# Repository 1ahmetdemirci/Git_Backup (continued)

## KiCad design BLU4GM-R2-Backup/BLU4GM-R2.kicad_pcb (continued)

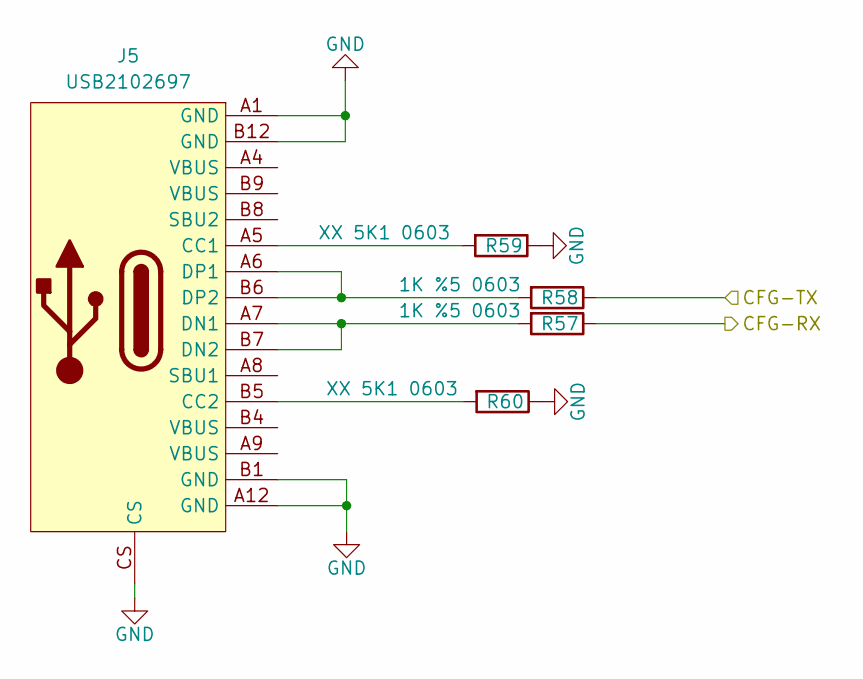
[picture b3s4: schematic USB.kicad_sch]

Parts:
J5: USB2102697
R57, R58: 1K %5 0603; R_0603_1608Metric
R59, R60: XX 5K1 0603; R_0603_1608Metric

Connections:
/MCU/CFG-RX: R57.1; also elsewhere on the board
/MCU/CFG-TX: R58.1; also elsewhere on the board
GND: J5.A1 (GND), J5.A12 (GND), J5.B1 (GND), J5.B12 (GND), J5.CS, R59.1, R60.1; also elsewhere on the board
unnamed: J5.A5 (CC1), R59.2
unnamed: J5.B5 (CC2), R60.2
unnamed: J5.A7 (DN1), J5.B7 (DN2), R57.2
unnamed: J5.A6 (DP1), J5.B6 (DP2), R58.2

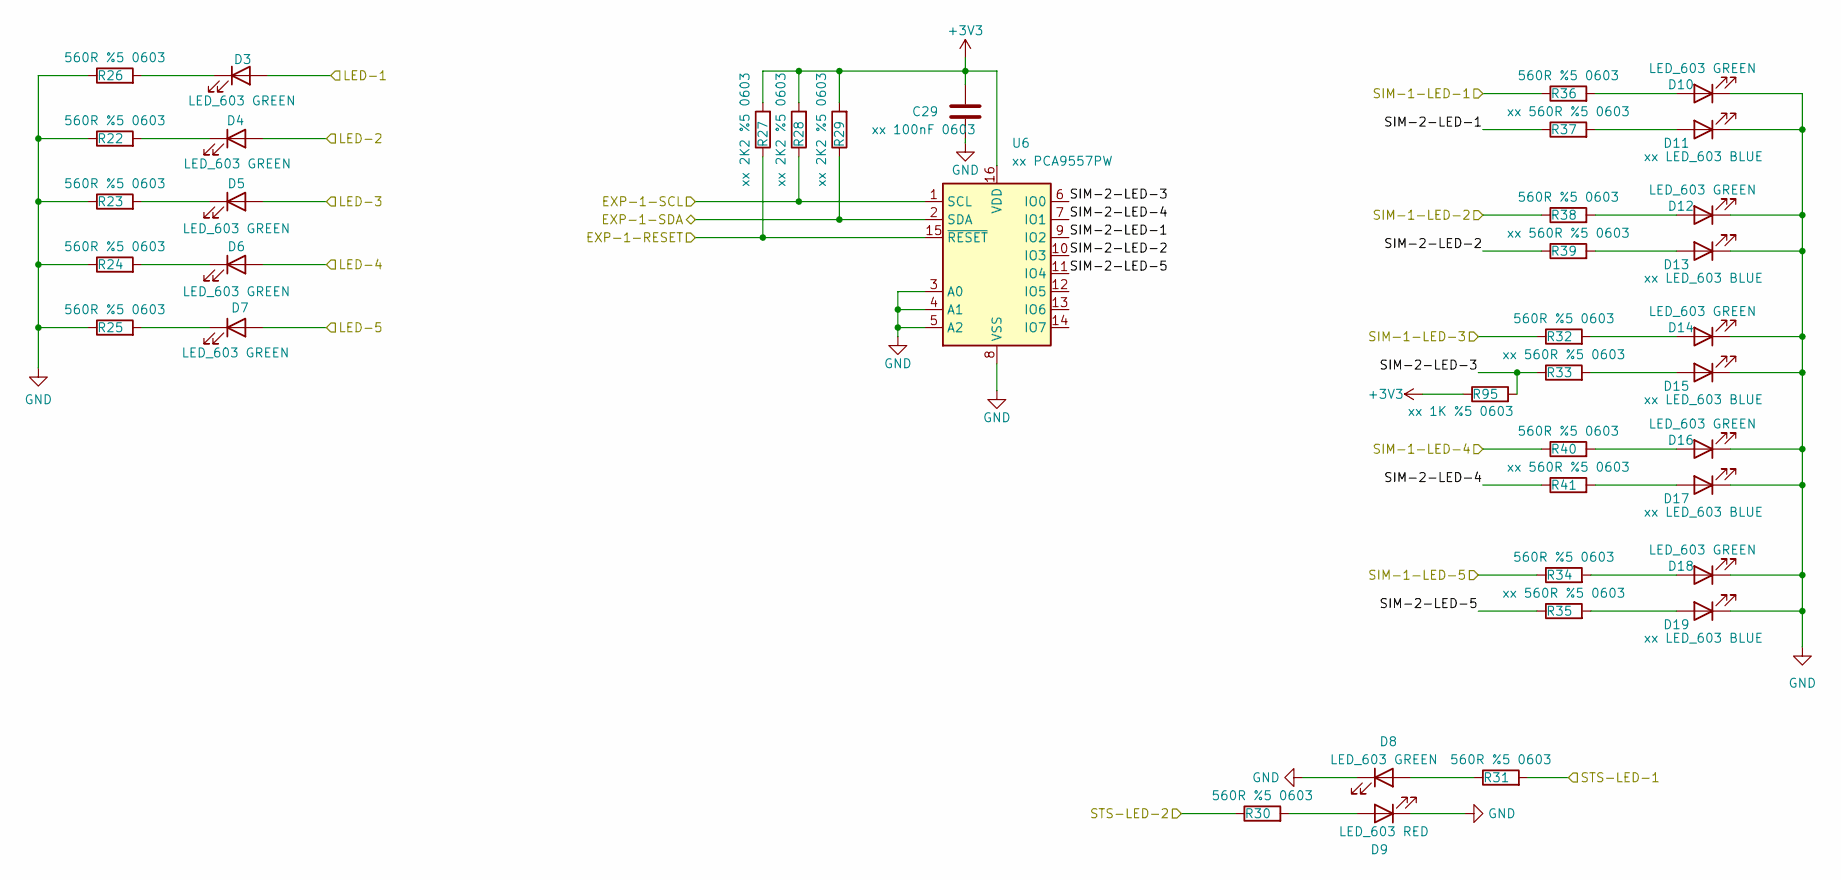
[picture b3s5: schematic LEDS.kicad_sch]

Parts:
C29: xx 100nF 0603; C_0603_1608Metric
D3, D4, D5, D6, D7, D8, D10, D12, D14, D16, D18: LED_603 GREEN; LED_0603_1608Metric
D9: LED_603 RED; LED_0603_1608Metric
D11, D13, D15, D17, D19: xx LED_603 BLUE; LED_0603_1608Metric
R22, R23, R24, R25, R26, R30, R31, R32, R34, R36, R38, R40: 560R %5 0603; R_0603_1608Metric
R27, R28, R29: xx 2K2 %5 0603; R_0603_1608Metric
R33, R35, R37, R39, R41: xx 560R %5 0603; R_0603_1608Metric
R95: xx 1K %5 0603; R_0603_1608Metric
U6: xx PCA9557PW; TSSOP-16_4.4x5mm_P0.65mm

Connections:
+3V3: C29.1, R27.2, R28.2, R29.2, R95.1, U6.16 (VDD); also elsewhere on the board
/LEDS/EXP-1-RESET: R27.1, U6.15 (~RESET); also elsewhere on the board
/LEDS/EXP-1-SCL: R28.1, U6.1 (SCL); also elsewhere on the board
/LEDS/EXP-1-SDA: R29.1, U6.2 (SDA); also elsewhere on the board
/LEDS/LED-1: D3.2 (A); also elsewhere on the board
/LEDS/LED-2: D4.2 (A); also elsewhere on the board
/LEDS/LED-3: D5.2 (A); also elsewhere on the board
/LEDS/LED-4: D6.2 (A); also elsewhere on the board
/LEDS/LED-5: D7.2 (A); also elsewhere on the board
/LEDS/SIM-1-LED-1: R36.1; also elsewhere on the board
/LEDS/SIM-1-LED-2: R38.1; also elsewhere on the board
/LEDS/SIM-1-LED-3: R32.1; also elsewhere on the board
/LEDS/SIM-1-LED-4: R40.1; also elsewhere on the board
/LEDS/SIM-1-LED-5: R34.1; also elsewhere on the board
/LEDS/SIM-2-LED-1: R37.1, U6.9 (IO2)
/LEDS/SIM-2-LED-2: R39.1, U6.10 (IO3)
/LEDS/SIM-2-LED-3: R33.1, R95.2, U6.6 (IO0)
/LEDS/SIM-2-LED-4: R41.1, U6.7 (IO1)
/LEDS/SIM-2-LED-5: R35.1, U6.11 (IO4)
/LEDS/STS-LED-1: R31.2; also elsewhere on the board
/LEDS/STS-LED-2: R30.1; also elsewhere on the board
GND: C29.2, D8.1 (K), D9.1 (K), D10.1 (K), D11.1 (K), D12.1 (K), D13.1 (K), D14.1 (K), D15.1 (K), D16.1 (K), D17.1 (K), D18.1 (K), D19.1 (K), R22.1, R23.1, R24.1, R25.1, R26.1, U6.3 (A0), U6.4 (A1), U6.5 (A2), U6.8 (VSS); also elsewhere on the board
unnamed: D3.1 (K), R26.2
unnamed: D4.1 (K), R22.2
unnamed: D5.1 (K), R23.2
unnamed: D6.1 (K), R24.2
unnamed: D7.1 (K), R25.2
unnamed: D8.2 (A), R31.1
unnamed: D9.2 (A), R30.2
unnamed: D10.2 (A), R36.2
unnamed: D11.2 (A), R37.2
unnamed: D12.2 (A), R38.2
unnamed: D13.2 (A), R39.2
unnamed: D14.2 (A), R32.2
unnamed: D15.2 (A), R33.2
unnamed: D16.2 (A), R40.2
unnamed: D17.2 (A), R41.2
unnamed: D18.2 (A), R34.2
unnamed: D19.2 (A), R35.2

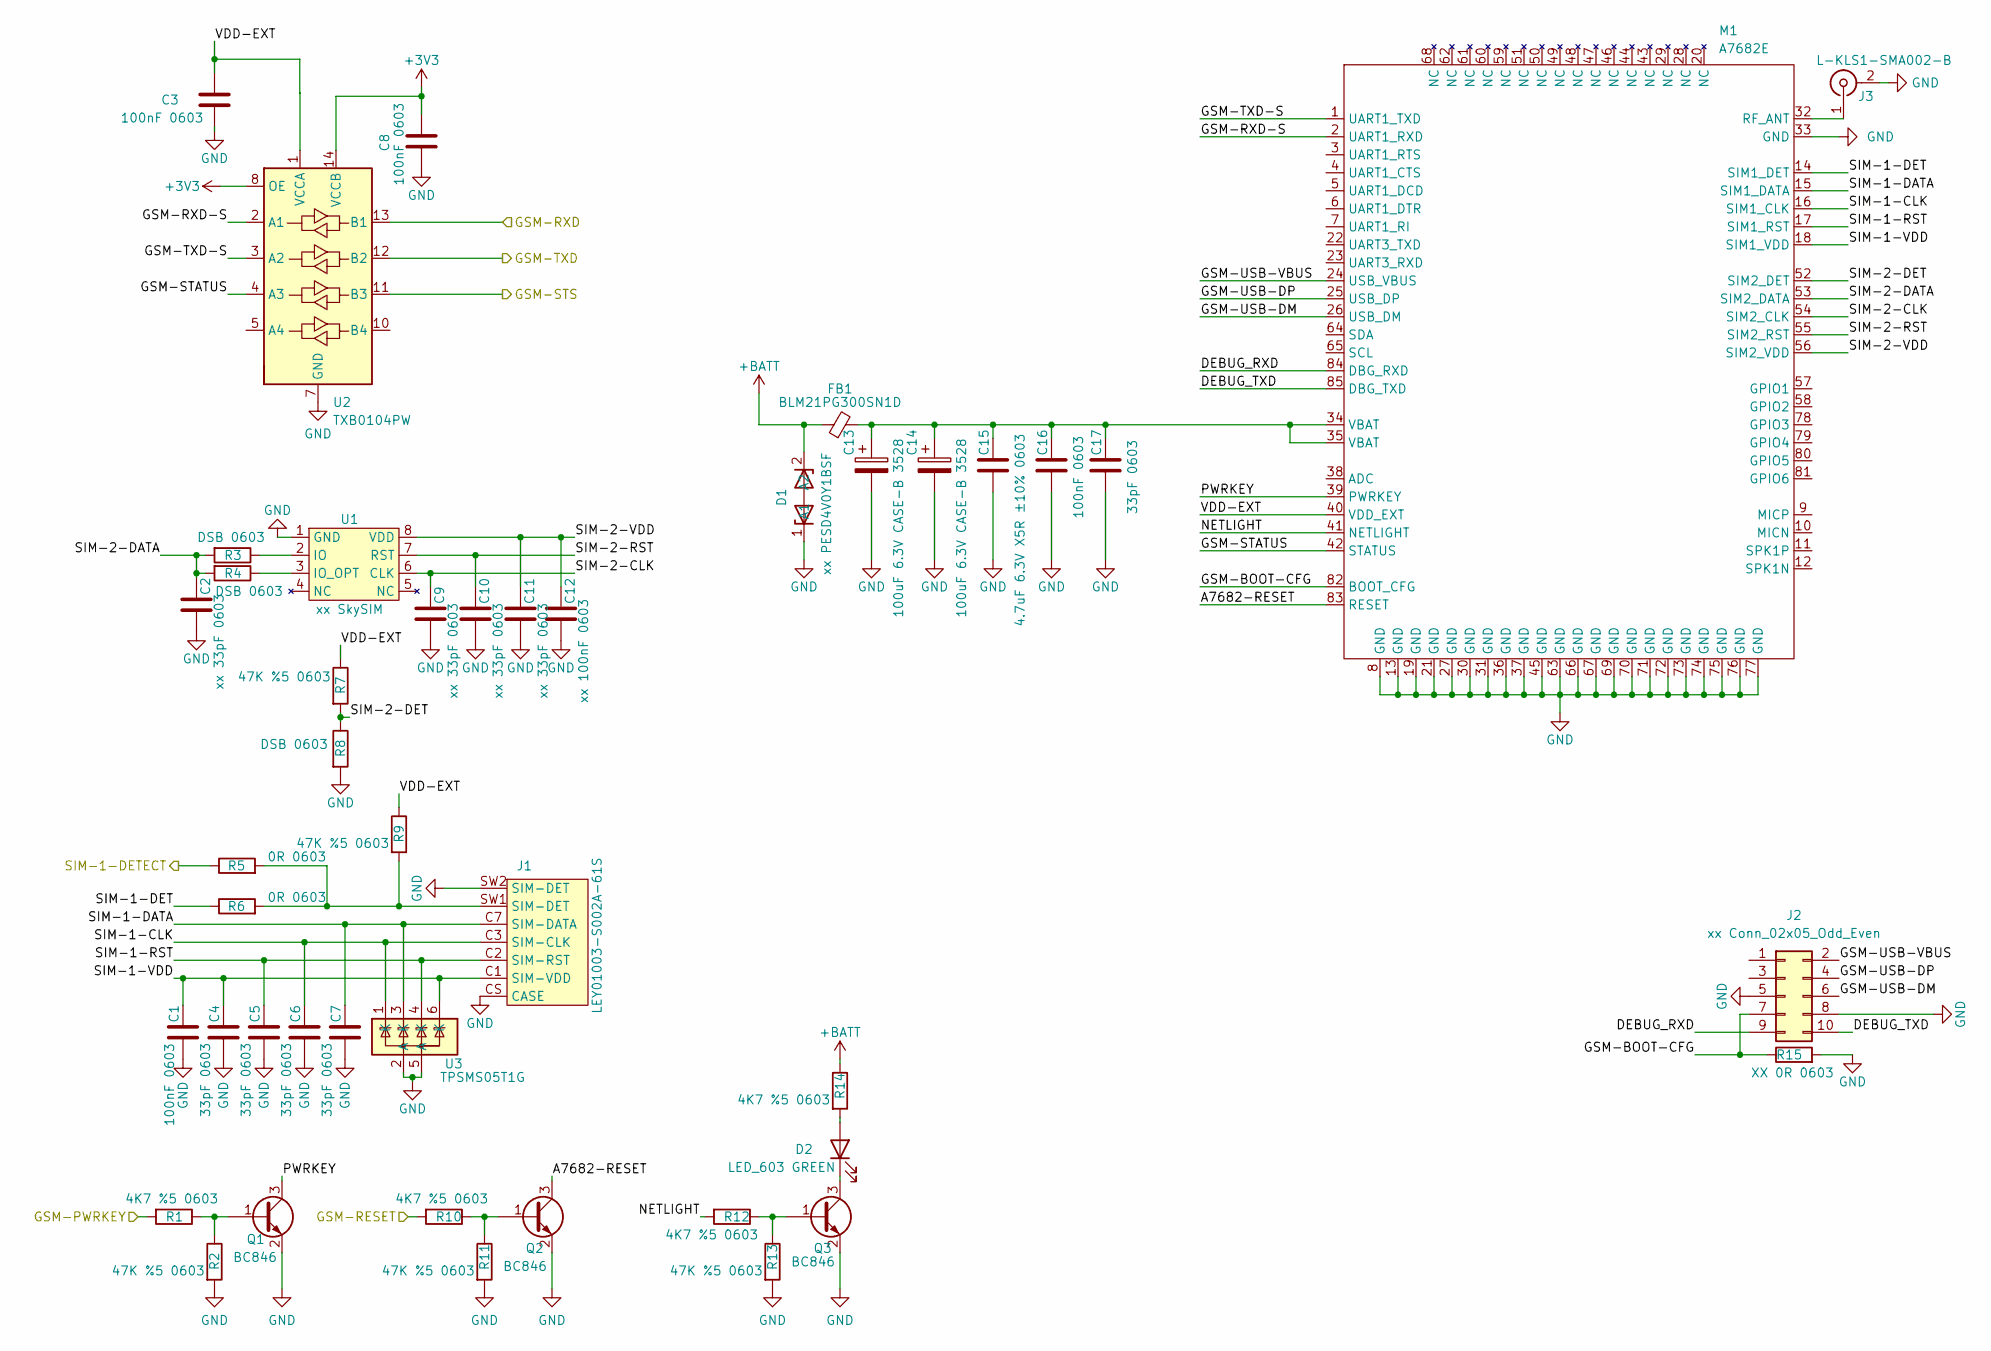
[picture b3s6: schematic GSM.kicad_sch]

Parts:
C1, C3, C8, C16: 100nF 0603; C_0603_1608Metric
C2, C9, C10, C11: xx 33pF 0603; C_0603_1608Metric
C4, C5, C6, C7, C17: 33pF 0603; C_0603_1608Metric
C12: xx 100nF 0603; C_0603_1608Metric
C13, C14: 100uF 6.3V CASE-B 3528; CP_EIA-3528-12_Kemet-T
C15: 4.7uF 6.3V X5R ±10% 0603; C_0603_1608Metric
D1: xx PESD4V0Y1BSF; PESD4V0Y1BSF
D2: LED_603 GREEN; LED_0603_1608Metric
FB1: BLM21PG300SN1D; L_0805_2012Metric
J1: LEY01003-S002A-61S
J2: xx Conn_02x05_Odd_Even; PinHeader_2x05_P1.27mm_Vertical
J3: L-KLS1-SMA002-B; SMA_Amphenol_132203-12_Horizontal
M1: A7682E
Q1, Q2, Q3: BC846; SOT-23
R1, R10, R12, R14: 4K7 %5 0603; R_0603_1608Metric
R2, R7, R9, R11, R13: 47K %5 0603; R_0603_1608Metric
R3, R4, R8: DSB 0603; R_0603_1608Metric
R5, R6: 0R 0603; R_0603_1608Metric
R15: XX 0R 0603; R_0603_1608Metric
U1: xx SkySIM; SOIC-8
U2: TXB0104PW; TSSOP-14_4.4x5mm_P0.65mm
U3: TPSMS05T1G

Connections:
+3V3: C8.1, U2.8 (OE), U2.14 (VCCB); also elsewhere on the board
+BATT: D1.2 (A2), FB1.1, R14.1; also elsewhere on the board
/GSM/A7682-RESET: M1.83 (RESET), Q2.3 (C)
/GSM/DEBUG_RXD: J2.9, M1.84 (DBG_RXD)
/GSM/DEBUG_TXD: J2.10, M1.85 (DBG_TXD)
/GSM/GSM-BOOT-CFG: J2.7, M1.82 (BOOT_CFG), R15.1
/GSM/GSM-PWRKEY: R1.2; also elsewhere on the board
/GSM/GSM-RESET: R10.2; also elsewhere on the board
/GSM/GSM-RXD: U2.13 (B1); also elsewhere on the board
/GSM/GSM-RXD-S: M1.2 (UART1_RXD), U2.2 (A1)
/GSM/GSM-STATUS: M1.42 (STATUS), U2.4 (A3)
/GSM/GSM-STS: U2.11 (B3); also elsewhere on the board
/GSM/GSM-TXD: U2.12 (B2); also elsewhere on the board
/GSM/GSM-TXD-S: M1.1 (UART1_TXD), U2.3 (A2)
/GSM/GSM-USB-DM: J2.6, M1.26 (USB_DM)
/GSM/GSM-USB-DP: J2.4, M1.25 (USB_DP)
/GSM/GSM-USB-VBUS: J2.2, M1.24 (USB_VBUS)
/GSM/NETLIGHT: M1.41 (NETLIGHT), R12.2
/GSM/PWRKEY: M1.39 (PWRKEY), Q1.3 (C)
/GSM/SIM-1-CLK: C6.1, J1.C3 (SIM-CLK), M1.16 (SIM1_CLK), U3.1 (K)
/GSM/SIM-1-DATA: C7.1, J1.C7 (SIM-DATA), M1.15 (SIM1_DATA), U3.3 (K)
/GSM/SIM-1-DET: M1.14 (SIM1_DET), R6.1
/GSM/SIM-1-DETECT: R5.1; also elsewhere on the board
/GSM/SIM-1-RST: C5.1, J1.C2 (SIM-RST), M1.17 (SIM1_RST), U3.4 (K)
/GSM/SIM-1-VDD: C1.1, C4.1, J1.C1 (SIM-VDD), M1.18 (SIM1_VDD), U3.6 (K)
/GSM/SIM-2-CLK: C9.1, M1.54 (SIM2_CLK), U1.6 (CLK)
/GSM/SIM-2-DATA: C2.1, M1.53 (SIM2_DATA), R3.2, R4.2
/GSM/SIM-2-DET: M1.52 (SIM2_DET), R7.2, R8.1
/GSM/SIM-2-RST: C10.1, M1.55 (SIM2_RST), U1.7 (RST)
/GSM/SIM-2-VDD: C11.1, C12.1, M1.56 (SIM2_VDD), U1.8 (VDD)
/GSM/VDD-EXT: C3.1, M1.40 (VDD_EXT), R7.1, R9.1, U2.1 (VCCA)
GND: C1.2, C2.2, C3.2, C4.2, C5.2, C6.2, C7.2, C8.2, C9.2, C10.2, C11.2, C12.2, C13.2, C14.2, C15.2, C16.2, C17.2, D1.1 (A1), J1.CS (CASE), J1.SW2 (SIM-DET), J2.5, J2.8, J3.2 (Ext), M1.8 (GND), M1.13 (GND), M1.19 (GND), M1.21 (GND), M1.27 (GND), M1.30 (GND), M1.31 (GND), M1.33 (GND), M1.36 (GND), M1.37 (GND), M1.45 (GND), M1.63 (GND), M1.66 (GND), M1.67 (GND), M1.69 (GND), M1.70 (GND), M1.71 (GND), M1.72 (GND), M1.73 (GND), M1.74 (GND), M1.75 (GND), M1.76 (GND), M1.77 (GND), Q1.2 (E), Q2.2 (E), Q3.2 (E), R2.2, R8.2, R11.2, R13.2, R15.2, U1.1 (GND), U2.7 (GND), U3.2 (A), U3.5 (A); also elsewhere on the board
unnamed: C13.1, C14.1, C15.1, C16.1, C17.1, FB1.2, M1.34 (VBAT), M1.35 (VBAT)
unnamed: D2.2 (A), R14.2
unnamed: D2.1 (K), Q3.3 (C)
unnamed: J1.SW1 (SIM-DET), R5.2, R6.2, R9.2
unnamed: J3.1 (In), M1.32 (RF_ANT)
unnamed: Q1.1 (B), R1.1, R2.1
unnamed: Q2.1 (B), R10.1, R11.1
unnamed: Q3.1 (B), R12.1, R13.1
unnamed: R3.1, U1.2 (IO)
unnamed: R4.1, U1.3 (IO_OPT)

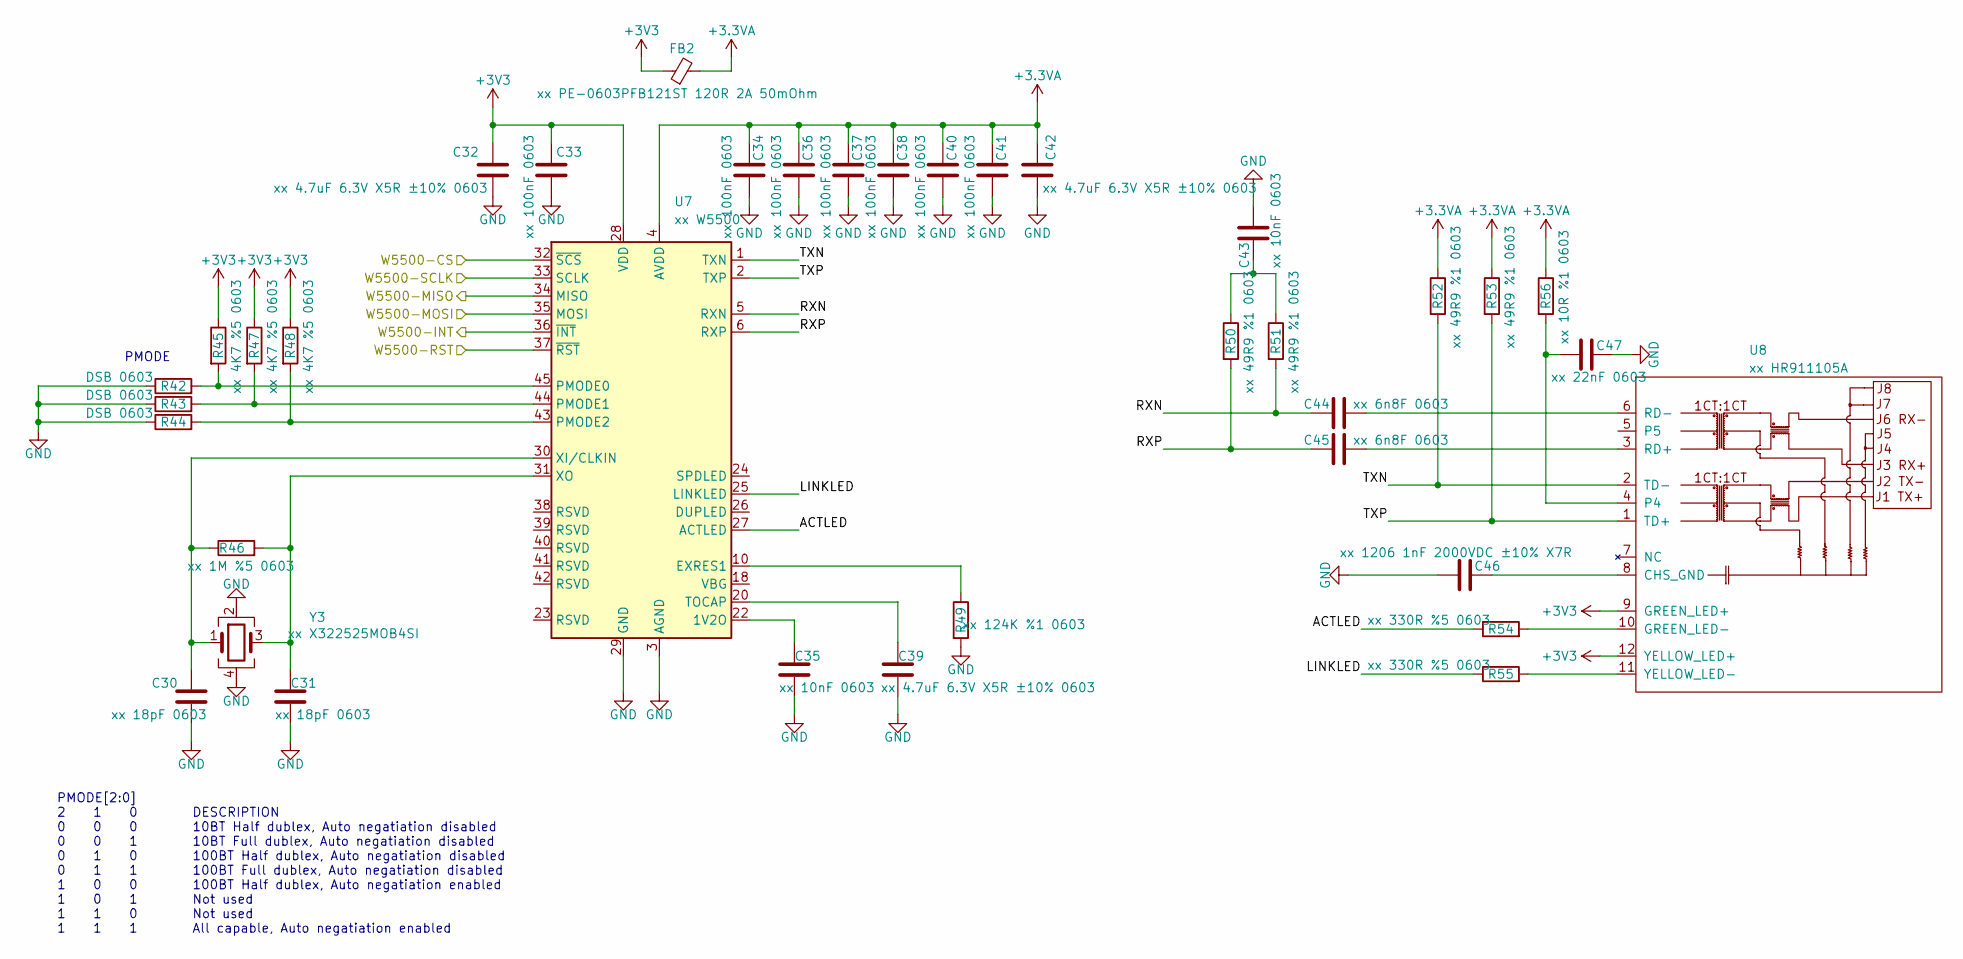
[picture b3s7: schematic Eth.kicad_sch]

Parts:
C30, C31: xx 18pF 0603; C_0603_1608Metric
C32, C39, C42: xx 4.7uF 6.3V X5R ±10% 0603; C_0603_1608Metric
C33, C34, C36, C37, C38, C40, C41: xx 100nF 0603; C_0603_1608Metric
C35, C43: xx 10nF 0603; C_0603_1608Metric
C44, C45: xx 6n8F 0603; C_0603_1608Metric
C46: xx 1206 1nF 2000VDC ±10% X7R; C_1206_3216Metric
C47: xx 22nF 0603; C_0603_1608Metric
FB2: xx PE-0603PFB121ST 120R 2A 50mOhm; L_0603_1608Metric
R42, R43, R44: DSB 0603; R_0603_1608Metric
R45, R47, R48: xx 4K7 %5 0603; R_0603_1608Metric
R46: xx 1M %5 0603; R_0603_1608Metric
R49: xx 124K %1 0603; R_0603_1608Metric
R50, R51, R52, R53: xx 49R9 %1 0603; R_0603_1608Metric
R54, R55: xx 330R %5 0603; R_0603_1608Metric
R56: xx 10R %1 0603; R_0603_1608Metric
U7: xx W5500; LQFP-48_7x7mm_P0.5mm
U8: xx HR911105A; HR911105a
Y3: xx X322525MOB4SI; Crystal_SMD_3225-4Pin_3.2x2.5mm

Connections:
+3.3VA: C34.2, C36.2, C37.2, C38.2, C40.2, C41.2, C42.1, FB2.2, R52.1, R53.1, R56.1, U7.4 (AVDD), U7.8 (AVDD), U7.11 (AVDD), U7.15 (AVDD), U7.17 (AVDD), U7.21 (AVDD)
+3V3: C32.2, C33.2, FB2.1, R45.1, R47.1, R48.1, U7.28 (VDD), U8.9 (GREEN_LED+), U8.12 (YELLOW_LED+); also elsewhere on the board
/Eth/ACTLED: R54.1, U7.27 (ACTLED)
/Eth/LINKLED: R55.1, U7.25 (LINKLED)
/Eth/RXN: C44.2, R51.2, U7.5 (RXN)
/Eth/RXP: C45.2, R50.2, U7.6 (RXP)
/Eth/TXN: R52.2, U7.1 (TXN), U8.2 (TD-)
/Eth/TXP: R53.2, U7.2 (TXP), U8.1 (TD+)
/Eth/W5500-CS: U7.32 (~SCS); also elsewhere on the board
/Eth/W5500-INT: U7.36 (~INT); also elsewhere on the board
/Eth/W5500-MISO: U7.34 (MISO); also elsewhere on the board
/Eth/W5500-MOSI: U7.35 (MOSI); also elsewhere on the board
/Eth/W5500-RST: U7.37 (~RST); also elsewhere on the board
/Eth/W5500-SCLK: U7.33 (SCLK); also elsewhere on the board
GND: C30.2, C31.1, C32.1, C33.1, C34.1, C35.1, C36.1, C37.1, C38.1, C39.1, C40.1, C41.1, C42.2, C43.1, C46.1, C47.1, R42.1, R43.1, R44.1, R49.2, U7.3 (AGND), U7.9 (AGND), U7.14 (AGND), U7.16 (AGND), U7.19 (AGND), U7.29 (GND), U7.48 (AGND), Y3.2, Y3.4; also elsewhere on the board
unnamed: C43.2, R50.1, R51.1
unnamed: C35.2, U7.22 (1V2O)
unnamed: R49.1, U7.10 (EXRES1)
unnamed: R42.2, R45.2, U7.45 (PMODE0)
unnamed: R43.2, R47.2, U7.44 (PMODE1)
unnamed: R44.2, R48.2, U7.43 (PMODE2)
unnamed: C39.2, U7.20 (TOCAP)
unnamed: C30.1, R46.1, U7.30 (XI/CLKIN), Y3.1
unnamed: C31.2, R46.2, U7.31 (XO), Y3.3
unnamed: C46.2, U8.8 (CHS_GND)
unnamed: R54.2, U8.10 (GREEN_LED-)
unnamed: C47.2, R56.2, U8.4
unnamed: C45.1, U8.3 (RD+)
unnamed: C44.1, U8.6 (RD-)
unnamed: R55.2, U8.11 (YELLOW_LED-)

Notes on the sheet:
PMODE[2:0] 2 1 0 DESCRIPTION 0 0 0 10BT Half dublex, Auto negatiation disabled 0 0 1 10BT Full dublex, Auto negatiation disabled 0 1 0 100BT Half dublex, Auto negatiation disabled 0 1 1 100BT Full dublex, Auto negatiation disabled 1 0 0 100BT Half dublex, Auto negatiation enabled 1 0 1 Not used 1 1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
PMODE

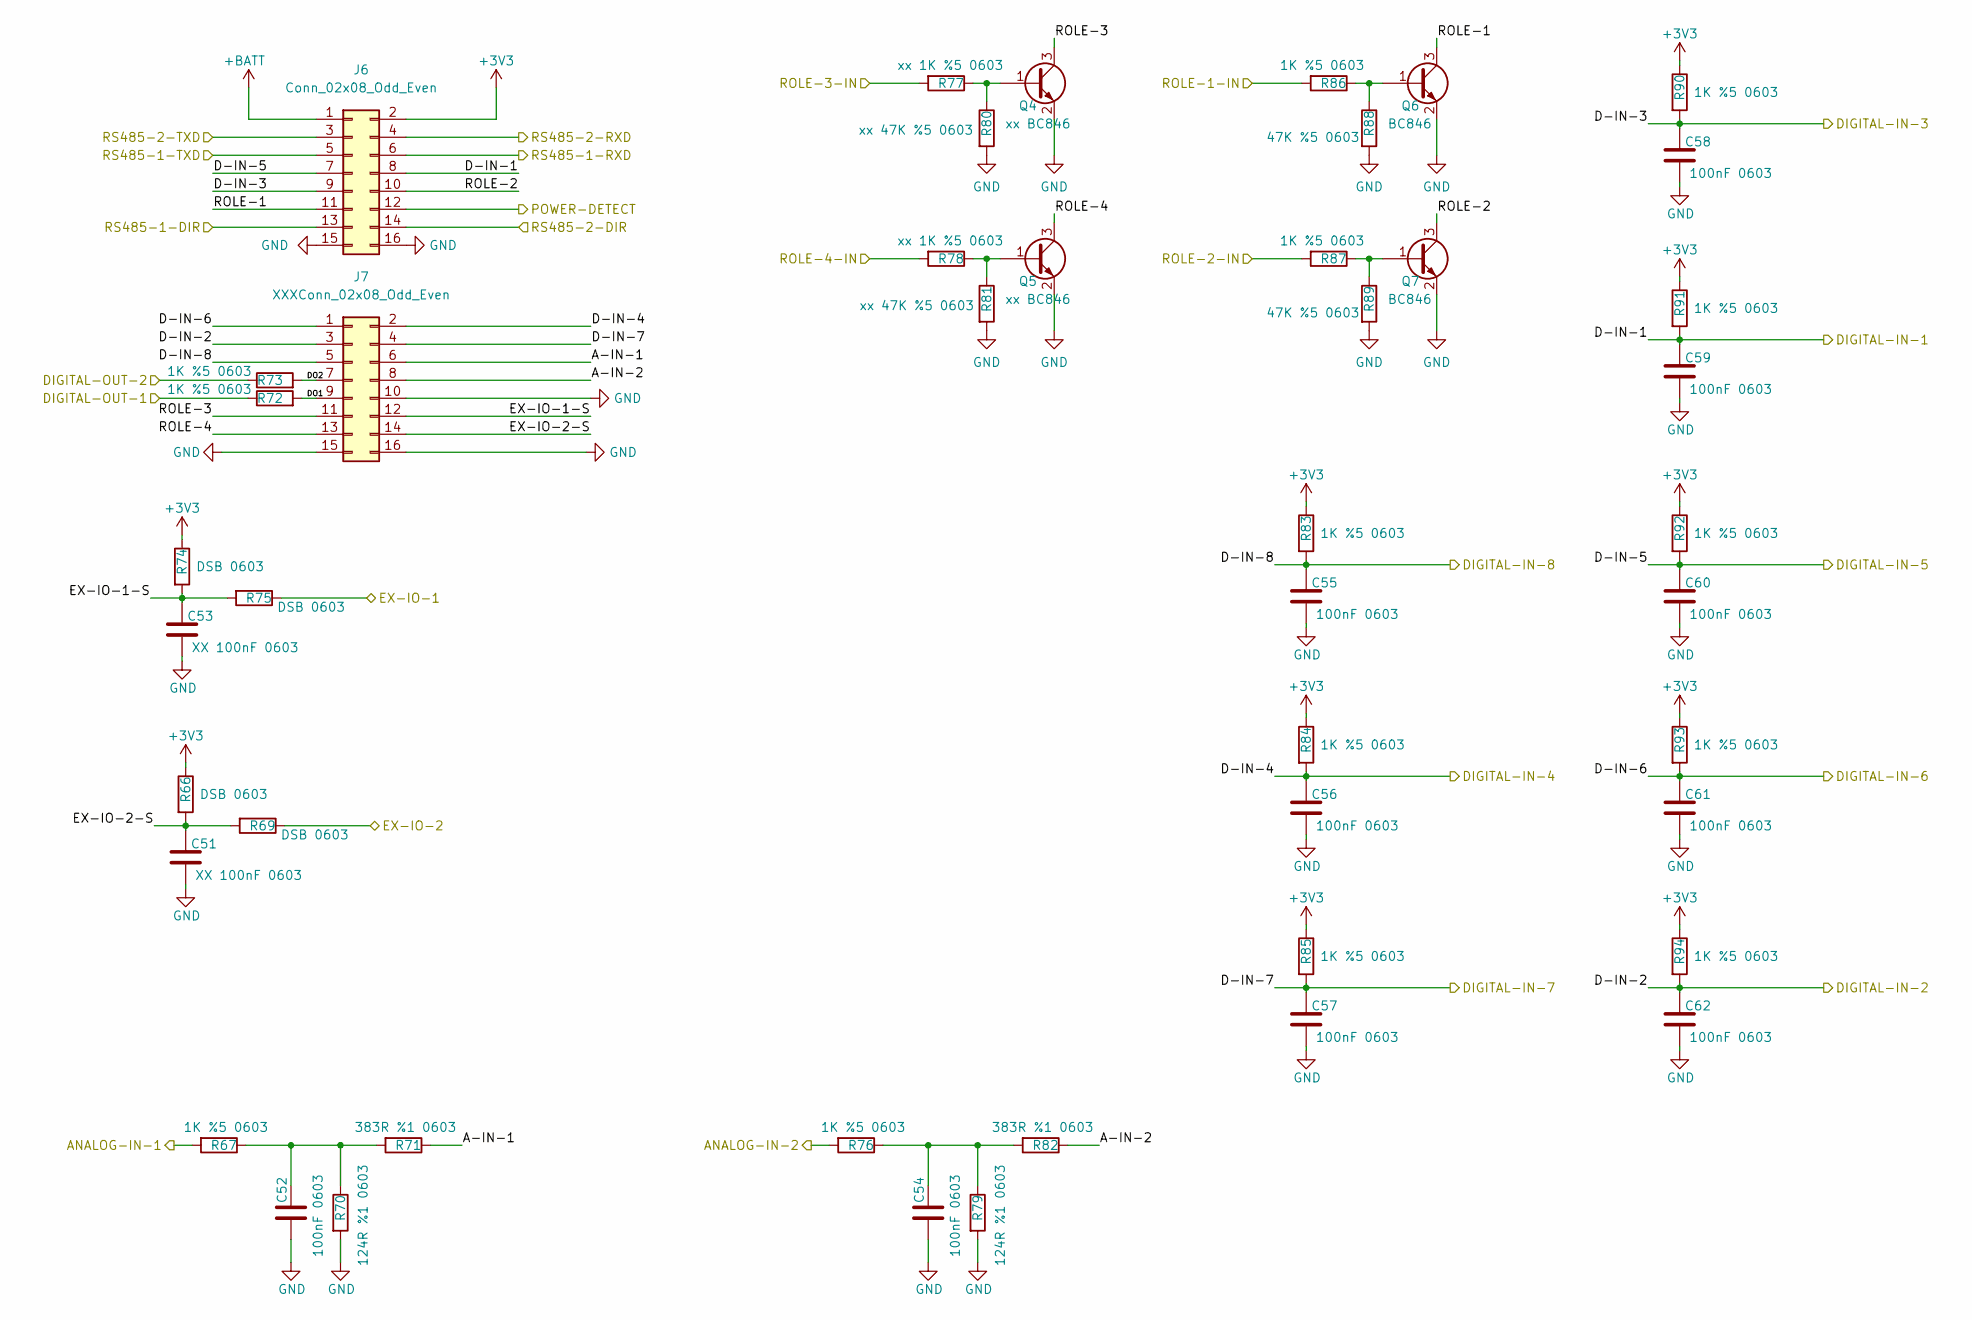
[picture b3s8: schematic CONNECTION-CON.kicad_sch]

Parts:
C51, C53: XX 100nF 0603; C_0603_1608Metric
C52, C54, C55, C56, C57, C58, C59, C60, C61, C62: 100nF 0603; C_0603_1608Metric
J6: Conn_02x08_Odd_Even; PinHeader_2x08_P2.54mm_Vertical
J7: XXXConn_02x08_Odd_Even; PinHeader_2x08_P2.54mm_Vertical
Q4, Q5: xx BC846; SOT-23
Q6, Q7: BC846; SOT-23
R66, R69, R74, R75: DSB 0603; R_0603_1608Metric
R67, R72, R73, R76, R83, R84, R85, R86, R87, R90, R91, R92, R93, R94: 1K %5 0603; R_0603_1608Metric
R70, R79: 124R %1 0603; R_0603_1608Metric
R71, R82: 383R %1 0603; R_0603_1608Metric
R77, R78: xx 1K %5 0603; R_0603_1608Metric
R80, R81: xx 47K %5 0603; R_0603_1608Metric
R88, R89: 47K %5 0603; R_0603_1608Metric

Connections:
+3V3: J6.2, R66.1, R74.1, R83.1, R84.1, R85.1, R90.1, R91.1, R92.1, R93.1, R94.1; also elsewhere on the board
+BATT: J6.1; also elsewhere on the board
/CONNECTION-CON/A-IN-1: J7.6, R71.1
/CONNECTION-CON/A-IN-2: J7.8, R82.1
/CONNECTION-CON/ANALOG-IN-1: R67.2; also elsewhere on the board
/CONNECTION-CON/ANALOG-IN-2: R76.2; also elsewhere on the board
/CONNECTION-CON/D-IN-1: C59.1, J6.8, R91.2; also elsewhere on the board
/CONNECTION-CON/D-IN-2: C62.1, J7.3, R94.2; also elsewhere on the board
/CONNECTION-CON/D-IN-3: C58.1, J6.9, R90.2; also elsewhere on the board
/CONNECTION-CON/D-IN-4: C56.1, J7.2, R84.2; also elsewhere on the board
/CONNECTION-CON/D-IN-5: C60.1, J6.7, R92.2; also elsewhere on the board
/CONNECTION-CON/D-IN-6: C61.1, J7.1, R93.2; also elsewhere on the board
/CONNECTION-CON/D-IN-7: C57.1, J7.4, R85.2; also elsewhere on the board
/CONNECTION-CON/D-IN-8: C55.1, J7.5, R83.2; also elsewhere on the board
/CONNECTION-CON/DIGITAL-OUT-1: R72.1; also elsewhere on the board
/CONNECTION-CON/DIGITAL-OUT-2: R73.1; also elsewhere on the board
/CONNECTION-CON/DO1: J7.9, R72.2
/CONNECTION-CON/DO2: J7.7, R73.2
/CONNECTION-CON/EX-IO-1: R75.1; also elsewhere on the board
/CONNECTION-CON/EX-IO-1-S: C53.1, J7.12, R74.2, R75.2
/CONNECTION-CON/EX-IO-2: R69.1; also elsewhere on the board
/CONNECTION-CON/EX-IO-2-S: C51.1, J7.14, R66.2, R69.2
/CONNECTION-CON/POWER-DETECT: J6.12; also elsewhere on the board
/CONNECTION-CON/ROLE-1: J6.11, Q6.3 (C)
/CONNECTION-CON/ROLE-1-IN: R86.2; also elsewhere on the board
/CONNECTION-CON/ROLE-2: J6.10, Q7.3 (C)
/CONNECTION-CON/ROLE-2-IN: R87.2; also elsewhere on the board
/CONNECTION-CON/ROLE-3: J7.11, Q4.3 (C)
/CONNECTION-CON/ROLE-3-IN: R77.2; also elsewhere on the board
/CONNECTION-CON/ROLE-4: J7.13, Q5.3 (C)
/CONNECTION-CON/ROLE-4-IN: R78.2; also elsewhere on the board
/CONNECTION-CON/RS485-1-DIR: J6.13; also elsewhere on the board
/CONNECTION-CON/RS485-1-RXD: J6.6; also elsewhere on the board
/CONNECTION-CON/RS485-1-TXD: J6.5; also elsewhere on the board
/CONNECTION-CON/RS485-2-DIR: J6.14; also elsewhere on the board
/CONNECTION-CON/RS485-2-RXD: J6.4; also elsewhere on the board
/CONNECTION-CON/RS485-2-TXD: J6.3; also elsewhere on the board
GND: C51.2, C52.2, C53.2, C54.2, C55.2, C56.2, C57.2, C58.2, C59.2, C60.2, C61.2, C62.2, J6.15, J6.16, J7.10, J7.15, J7.16, Q4.2 (E), Q5.2 (E), Q6.2 (E), Q7.2 (E), R70.2, R79.2, R80.2, R81.2, R88.2, R89.2; also elsewhere on the board
unnamed: C52.1, R67.1, R70.1, R71.2
unnamed: C54.1, R76.1, R79.1, R82.2
unnamed: Q4.1 (B), R77.1, R80.1
unnamed: Q5.1 (B), R78.1, R81.1
unnamed: Q6.1 (B), R86.1, R88.1
unnamed: Q7.1 (B), R87.1, R89.1

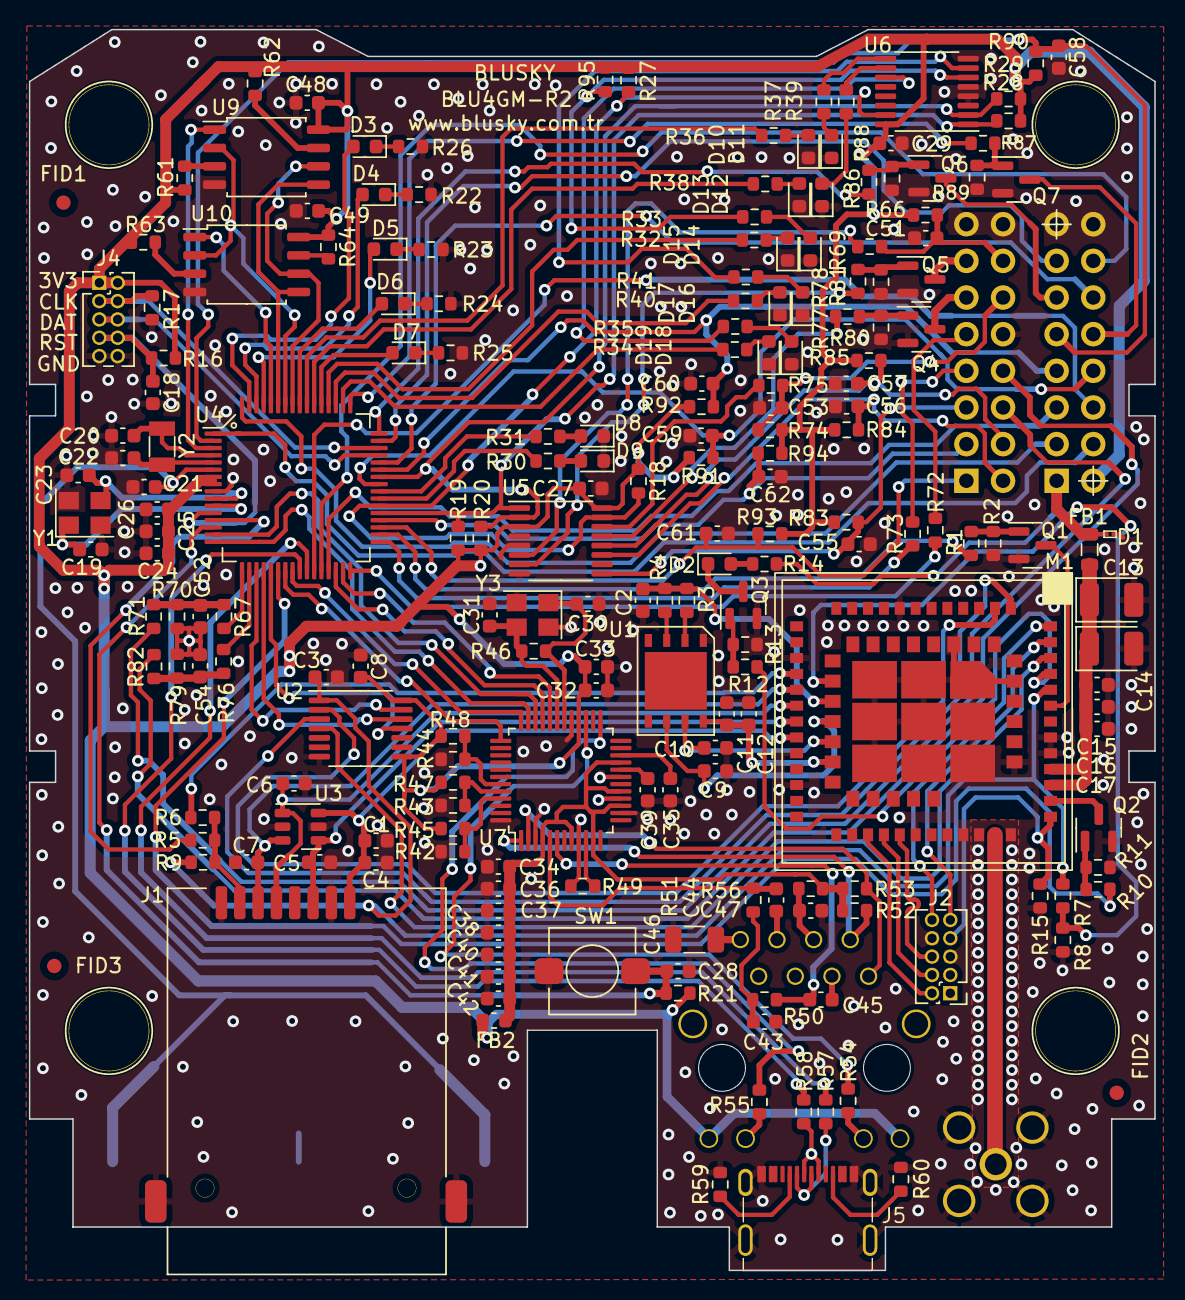
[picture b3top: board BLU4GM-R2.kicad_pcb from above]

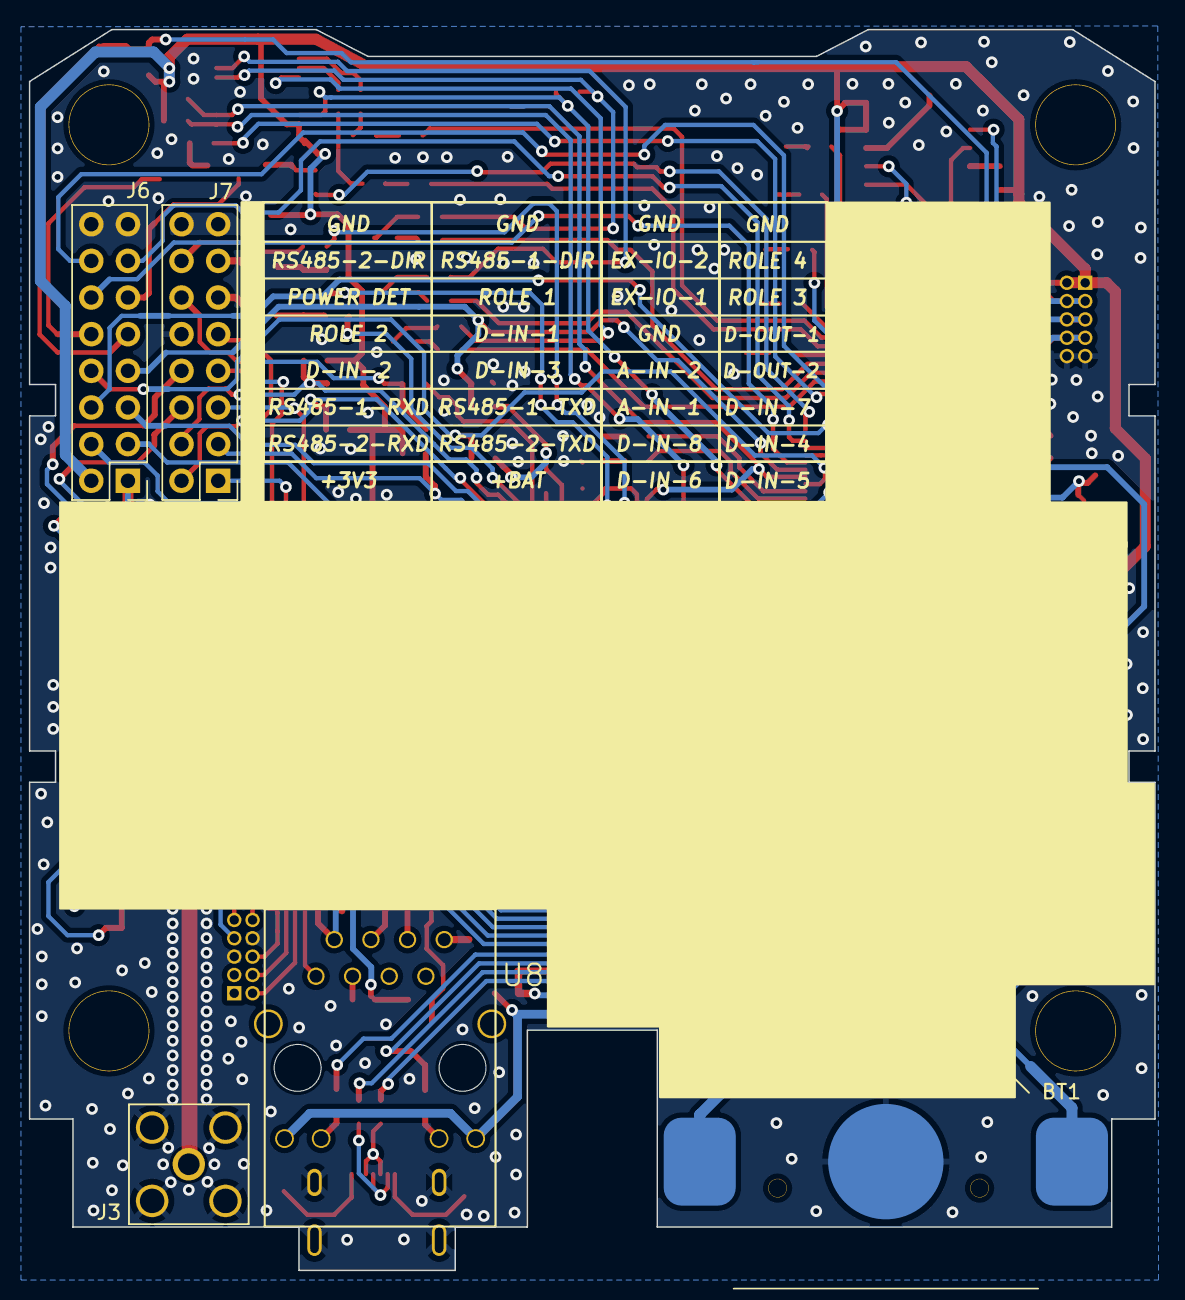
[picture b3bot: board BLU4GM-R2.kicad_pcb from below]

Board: 2 copper layers, 78.0 x 86.0 mm, 209 parts (5 on the bottom side), 172 nets.

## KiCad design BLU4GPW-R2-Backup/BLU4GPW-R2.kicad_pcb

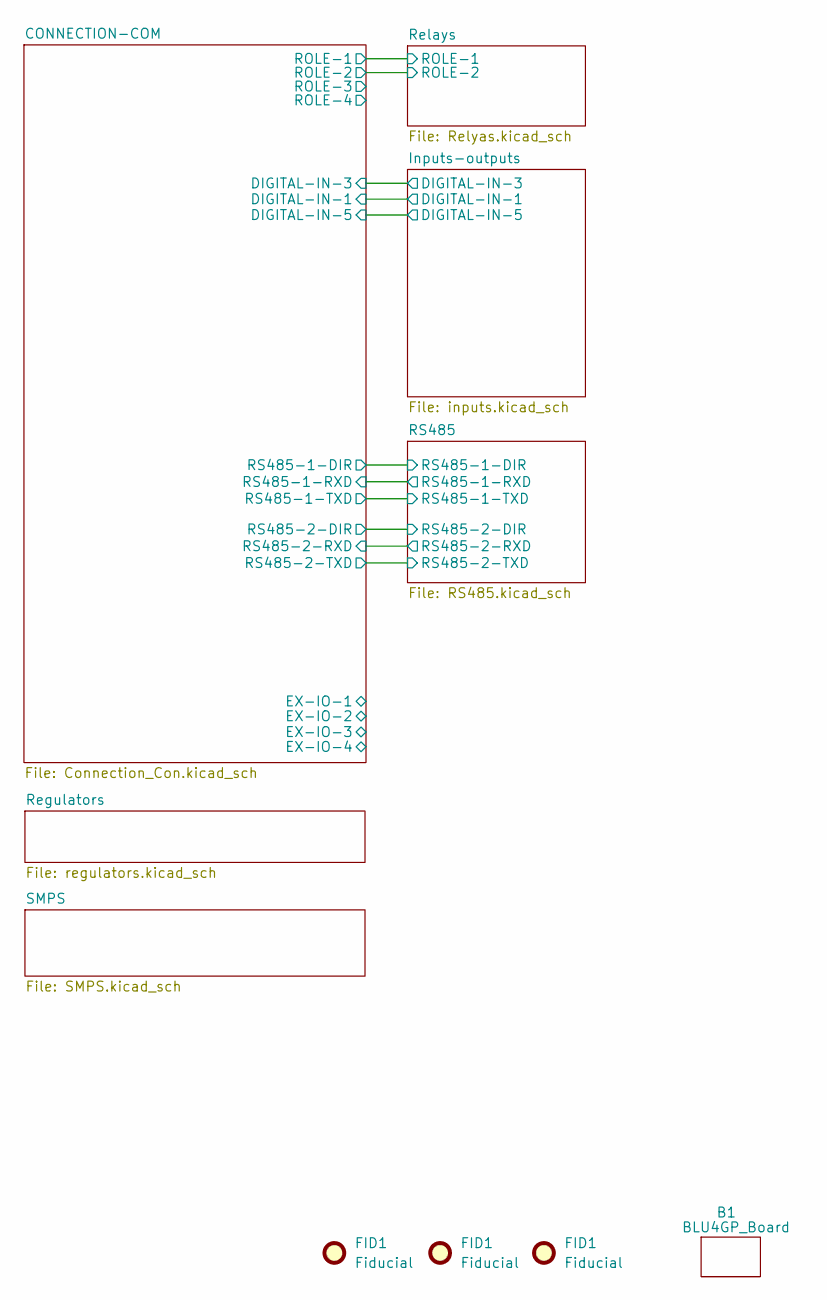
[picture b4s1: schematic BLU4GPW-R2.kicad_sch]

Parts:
B1: BLU4GP_Board; BLULC-Power
FID1: Fiducial; Fiducial_1mm_Mask2mm
